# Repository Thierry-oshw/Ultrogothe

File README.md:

# Ultrogothe
 Module STM32 debugger USB-C

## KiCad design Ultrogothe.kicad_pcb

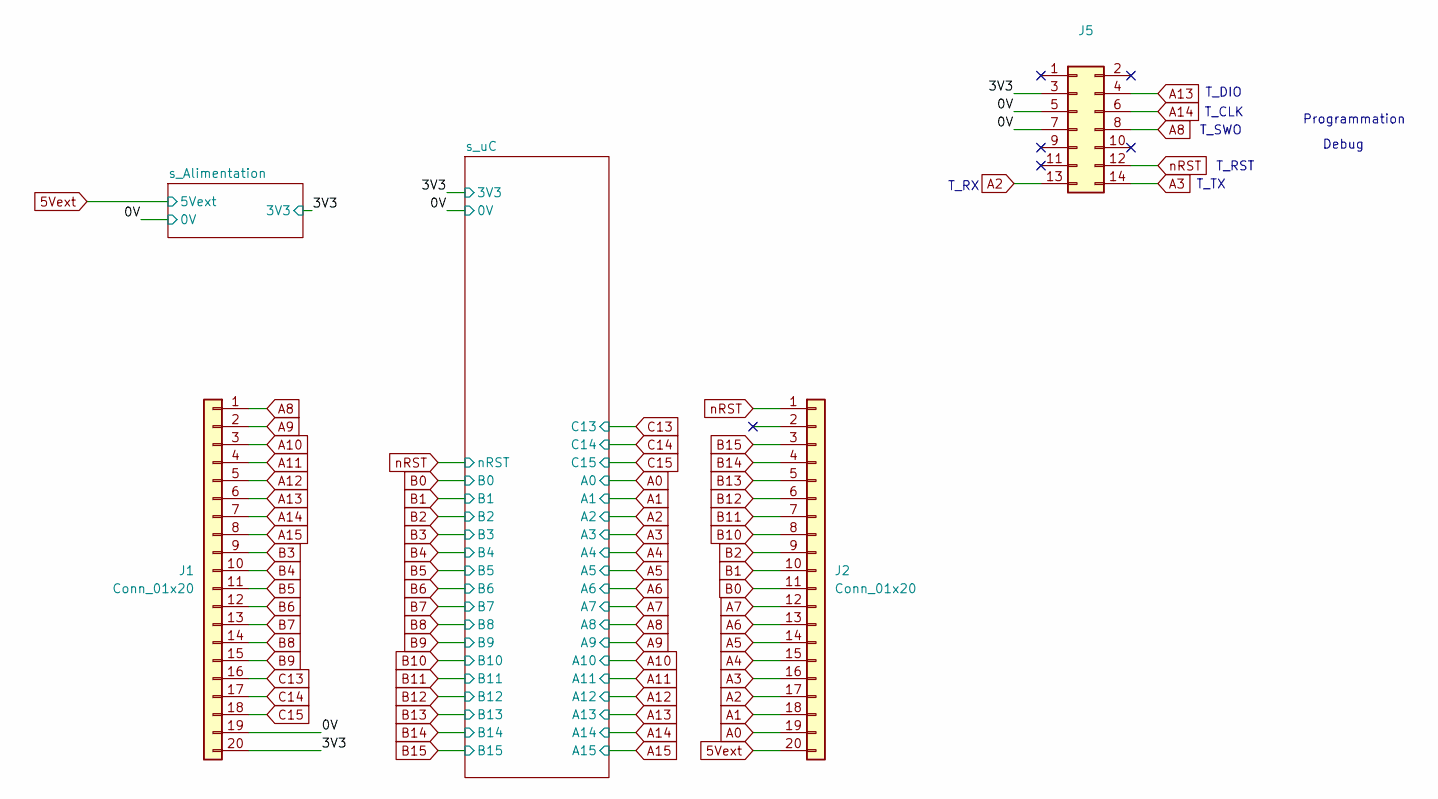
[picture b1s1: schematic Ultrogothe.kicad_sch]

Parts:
J1, J2: Conn_01x20; PinHeader_1x20_P2.54mm_Simple
J5: Conn_02x07_Odd_Even; PinHeader_2x07_P1.27mm_Vertical_SMD; LCSC C3975190

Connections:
5Vext: J2.20; also elsewhere on the board
/0V: J1.19, J5.5, J5.7; also elsewhere on the board
/3V3: J1.20, J5.3; also elsewhere on the board
A0: J2.19; also elsewhere on the board
A1: J2.18; also elsewhere on the board
A2: J2.17, J5.13; also elsewhere on the board
A3: J2.16, J5.14; also elsewhere on the board
A4: J2.15; also elsewhere on the board
A5: J2.14; also elsewhere on the board
A6: J2.13; also elsewhere on the board
A7: J2.12; also elsewhere on the board
A8: J1.1, J5.8; also elsewhere on the board
A9: J1.2; also elsewhere on the board
A10: J1.3; also elsewhere on the board
A11: J1.4; also elsewhere on the board
A12: J1.5; also elsewhere on the board
A13: J1.6, J5.4; also elsewhere on the board
A14: J1.7, J5.6; also elsewhere on the board
A15: J1.8; also elsewhere on the board
B0: J2.11; also elsewhere on the board
B1: J2.10; also elsewhere on the board
B2: J2.9; also elsewhere on the board
B3: J1.9; also elsewhere on the board
B4: J1.10; also elsewhere on the board
B5: J1.11; also elsewhere on the board
B6: J1.12; also elsewhere on the board
B7: J1.13; also elsewhere on the board
B8: J1.14; also elsewhere on the board
B9: J1.15; also elsewhere on the board
B10: J2.8; also elsewhere on the board
B11: J2.7; also elsewhere on the board
B12: J2.6; also elsewhere on the board
B13: J2.5; also elsewhere on the board
B14: J2.4; also elsewhere on the board
B15: J2.3; also elsewhere on the board
C13: J1.16; also elsewhere on the board
C14: J1.17; also elsewhere on the board
C15: J1.18; also elsewhere on the board
nRST: J2.1, J5.12; also elsewhere on the board

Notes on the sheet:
T_RX
T_TX
T_DIO
Programmation
T_CLK
Debug
T_SWO
T_RST

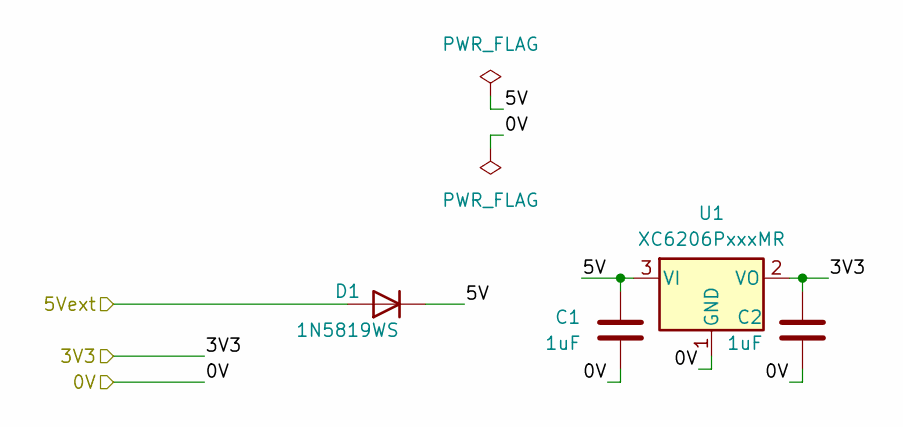
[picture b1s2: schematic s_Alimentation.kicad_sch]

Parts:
C1, C2: 1uF; C_0402_1005Metric; LCSC C52923
D1: 1N5819WS; D_SOD-323; LCSC C191023
U1: XC6206PxxxMR; SOT-23-3; LCSC C5446

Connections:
5Vext: D1.2 (A); also elsewhere on the board
/0V: C1.1, C2.1, U1.1 (GND); also elsewhere on the board
/3V3: C2.2, U1.2 (VO); also elsewhere on the board
/s_Alimentation/5V: C1.2, D1.1 (K), U1.3 (VI)

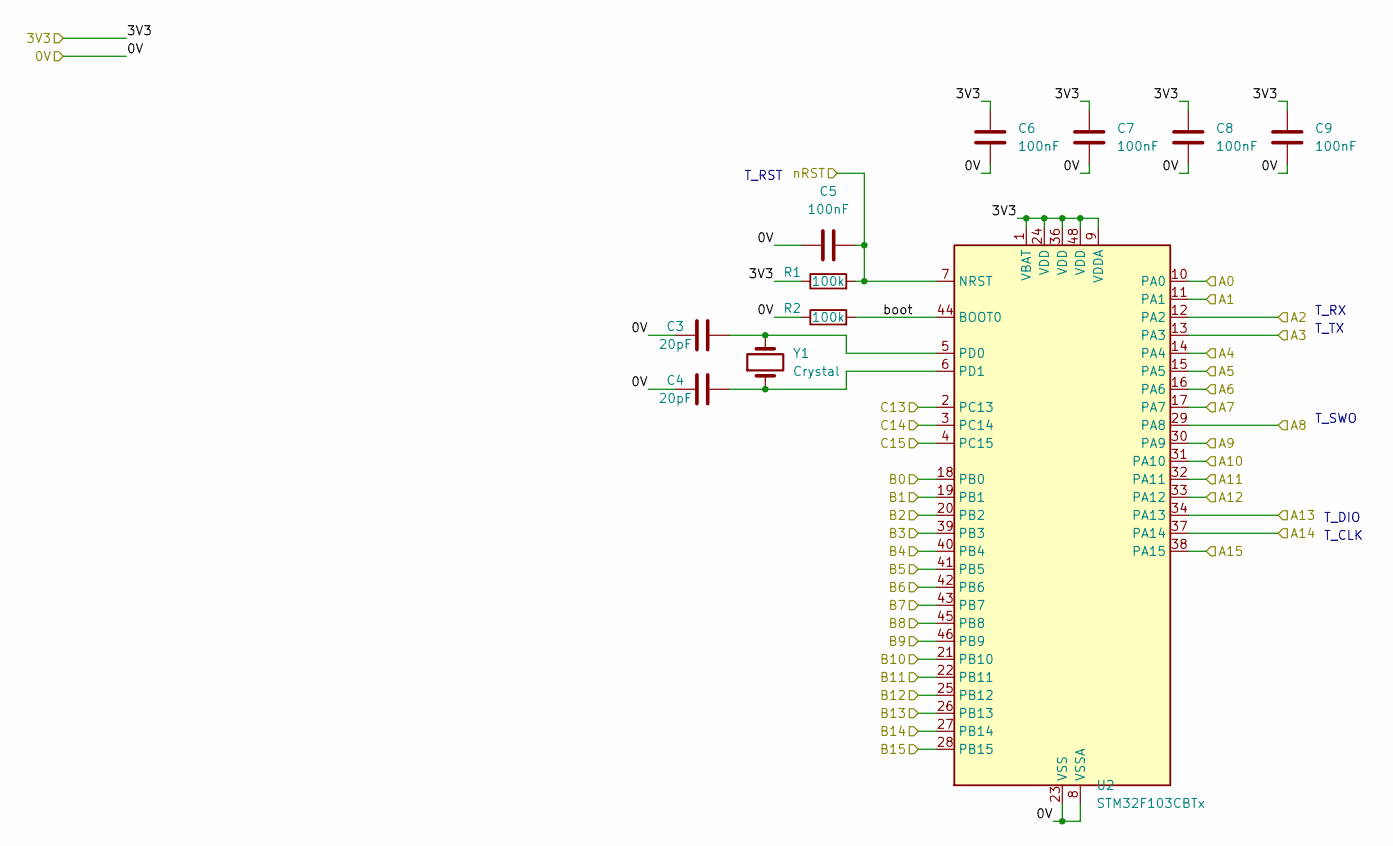
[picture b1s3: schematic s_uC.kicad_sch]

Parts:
C3, C4: 20pF; C_0402_1005Metric; LCSC C1554
C5, C6, C7, C8, C9: 100nF; C_0402_1005Metric; LCSC C1525
R1, R2: 100k; R_0402_1005Metric; LCSC C25741
U2: STM32F103CBTx; LQFP-48_7x7mm_P0.5mm; LCSC C8304
Y1: Crystal; Crystal_SMD_5032-2Pin_5.0x3.2mm; LCSC C115962

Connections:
/0V: C3.1, C4.1, C5.1, C6.1, C7.1, C8.1, C9.1, R2.1, U2.8 (VSSA), U2.23 (VSS), U2.35 (VSS), U2.47 (VSS); also elsewhere on the board
/3V3: C6.2, C7.2, C8.2, C9.2, R1.1, U2.1 (VBAT), U2.9 (VDDA), U2.24 (VDD), U2.36 (VDD), U2.48 (VDD); also elsewhere on the board
/s_uC/boot: R2.2, U2.44 (BOOT0)
A0: U2.10 (PA0); also elsewhere on the board
A1: U2.11 (PA1); also elsewhere on the board
A2: U2.12 (PA2); also elsewhere on the board
A3: U2.13 (PA3); also elsewhere on the board
A4: U2.14 (PA4); also elsewhere on the board
A5: U2.15 (PA5); also elsewhere on the board
A6: U2.16 (PA6); also elsewhere on the board
A7: U2.17 (PA7); also elsewhere on the board
A8: U2.29 (PA8); also elsewhere on the board
A9: U2.30 (PA9); also elsewhere on the board
A10: U2.31 (PA10); also elsewhere on the board
A11: U2.32 (PA11); also elsewhere on the board
A12: U2.33 (PA12); also elsewhere on the board
A13: U2.34 (PA13); also elsewhere on the board
A14: U2.37 (PA14); also elsewhere on the board
A15: U2.38 (PA15); also elsewhere on the board
B0: U2.18 (PB0); also elsewhere on the board
B1: U2.19 (PB1); also elsewhere on the board
B2: U2.20 (PB2); also elsewhere on the board
B3: U2.39 (PB3); also elsewhere on the board
B4: U2.40 (PB4); also elsewhere on the board
B5: U2.41 (PB5); also elsewhere on the board
B6: U2.42 (PB6); also elsewhere on the board
B7: U2.43 (PB7); also elsewhere on the board
B8: U2.45 (PB8); also elsewhere on the board
B9: U2.46 (PB9); also elsewhere on the board
B10: U2.21 (PB10); also elsewhere on the board
B11: U2.22 (PB11); also elsewhere on the board
B12: U2.25 (PB12); also elsewhere on the board
B13: U2.26 (PB13); also elsewhere on the board
B14: U2.27 (PB14); also elsewhere on the board
B15: U2.28 (PB15); also elsewhere on the board
C13: U2.2 (PC13); also elsewhere on the board
C14: U2.3 (PC14); also elsewhere on the board
C15: U2.4 (PC15); also elsewhere on the board
unnamed: C3.2, U2.5 (PD0), Y1.2
unnamed: C4.2, U2.6 (PD1), Y1.1
nRST: C5.2, R1.2, U2.7 (NRST); also elsewhere on the board

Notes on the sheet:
T_CLK
T_RX
T_SWO
T_RST
T_DIO
T_TX

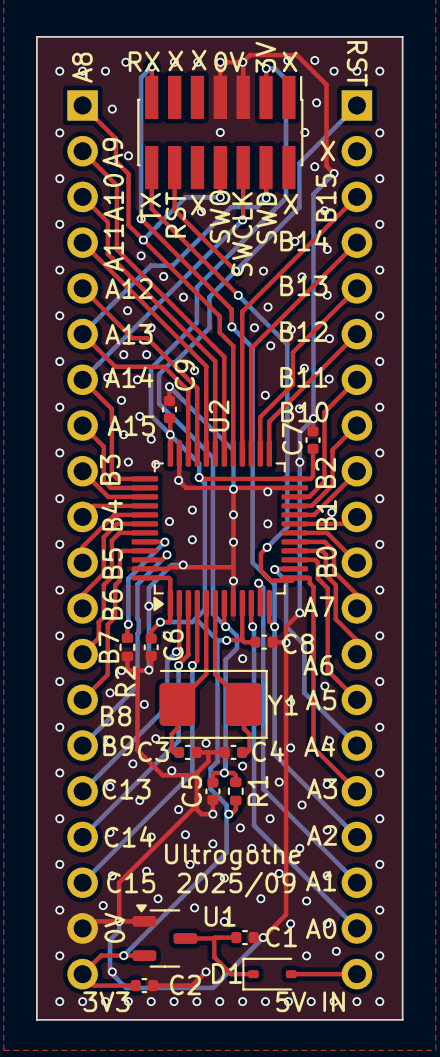
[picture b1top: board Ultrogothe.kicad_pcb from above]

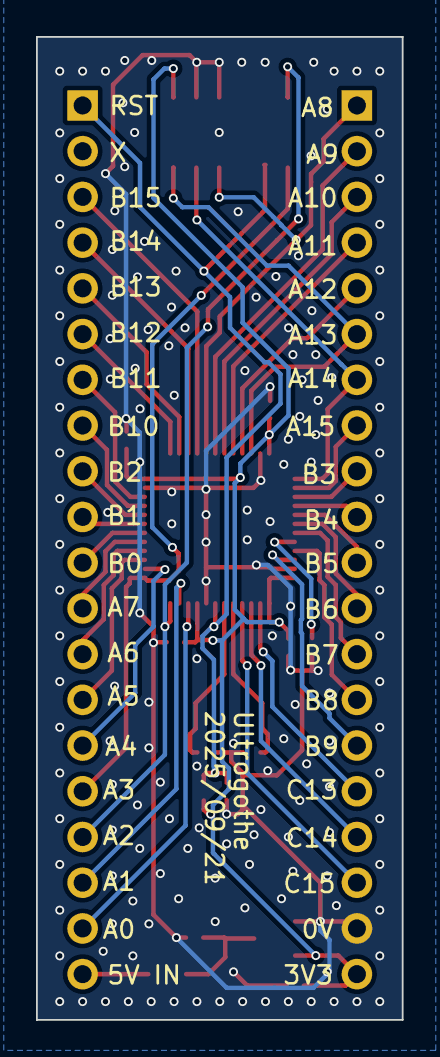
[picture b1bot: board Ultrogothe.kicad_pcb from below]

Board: 2 copper layers, 20.3 x 54.6 mm, 18 parts (2 on the bottom side), 43 nets.

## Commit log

2024-05-03 schéma premier jet
2024-05-03 pcb : mise en place pour forme en cours
2024-05-08 passif en 0402
2024-05-30 simplification
2024-05-30 renumerotation
2024-06-01 placement
2024-06-02 répartition pins encours
2024-06-06 répartition pins et routage
2024-08-03 routage fini
2024-10-10 Passage à kicad 8
    et correction des chemins spécifiques
2024-10-23 Chgt connecteur programmation
    passage à 2,54mm
    alignement avec grille
    silk: ajout pins
    maj schéma pour clarification
2024-10-23 vias et plans cuivres
2024-10-23 plugin + génération fichiers JLCPCB
2024-12-04 licence cern
2025-07-17 maj kicad v9
2025-09-15 changement connecteur prog/debug par ST14
2025-09-20 chgt ST14 en CMS et fabrication
